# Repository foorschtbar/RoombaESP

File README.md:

# RoombaESP

This project is a Add-On PCB for the Roomba vacuum cleaner robots of series 500/600/700. It uses the open interface of the Roomba to control the robot via a ESP8266 microcontroller. The PCB is designed to be mounted on top in a 3D printed case and add

- MQTT
- REST API
- Monitoring Interface
- OLED Screen
- Status LED

## PCB

## Case & Features

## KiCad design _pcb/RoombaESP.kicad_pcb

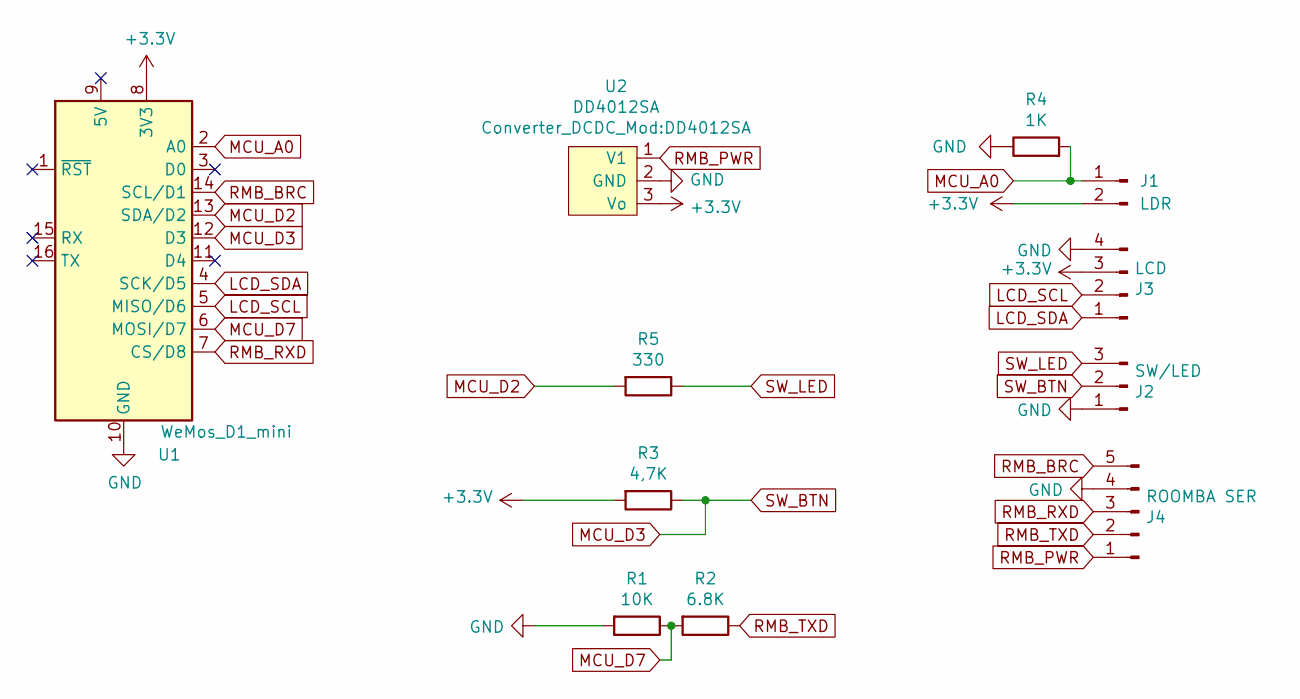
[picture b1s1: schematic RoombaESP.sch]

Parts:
J1: LDR; JST_PH_S2B-PH-K_1x02_P2.00mm_Horizontal
J2: SW/LED; JST_PH_S3B-PH-K_1x03_P2.00mm_Horizontal
J3: LCD; JST_PH_S4B-PH-K_1x04_P2.00mm_Horizontal
J4: ROOMBA SER; JST_PH_S5B-PH-K_1x05_P2.00mm_Horizontal
R1: 10K; R_0805_2012Metric_Pad1.20x1.40mm_HandSolder
R2: 6.8K; R_0805_2012Metric_Pad1.20x1.40mm_HandSolder
R3: 4,7K; R_0805_2012Metric_Pad1.20x1.40mm_HandSolder
R4: 1K; R_0805_2012Metric_Pad1.20x1.40mm_HandSolder
R5: 330; R_0805_2012Metric_Pad1.20x1.40mm_HandSolder
U1: WeMos_D1_mini; WEMOS_D1_mini_light
U2: DD4012SA

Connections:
+3V3: J1.2, J3.3, R3.2, U1.8 (3V3), U2.3 (Vo)
GND: J2.1, J3.4, J4.4, R1.2, R4.1, U1.10 (GND), U2.2 (GND)
LCD_SCL: J3.2, U1.5 (MISO/D6)
LCD_SDA: J3.1, U1.4 (SCK/D5)
MCU_A0: J1.1, R4.2, U1.2 (A0)
MCU_D2: R5.2, U1.13 (SDA/D2)
MCU_D3: J2.2, R3.1, U1.12 (D3)
MCU_D7: R1.1, R2.2, U1.6 (MOSI/D7)
RMB_BRC: J4.5, U1.14 (SCL/D1)
RMB_PWR: J4.1, U2.1 (V1)
RMB_RXD: J4.3, U1.7 (CS/D8)
RMB_TXD: J4.2, R2.1
SW_LED: J2.3, R5.1

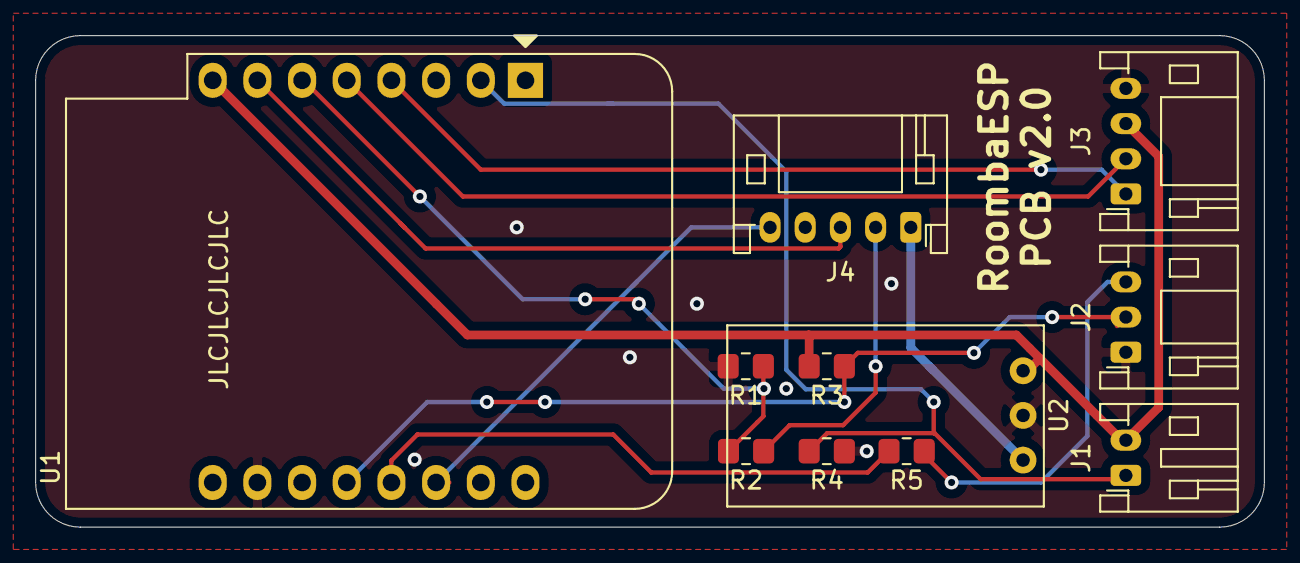
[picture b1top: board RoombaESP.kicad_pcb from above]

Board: 2 copper layers, 69.9 x 27.9 mm, 11 parts (0 on the bottom side), 13 nets.

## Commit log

2019-11-11 Fixes
2019-11-19 Fix sensor status problem with some yield()'s
2019-11-24 Finish API for Dock commands
2020-10-16 Rename Wifi signal quaility function and update .gitignore
2020-10-24 Implemented MQTT, removed REST API
2020-12-29 added oled boot screen
2020-12-29 removed travis ci file
2021-01-17 Added OLED Screen - add oled screen - remove log to SPIFF - other improvements
2021-01-17 Added Screen Switching and Timeout
2021-01-18 updates documentation
2021-01-19 Some improvments - added more screens - fix some issues with mqtt topics - add a lot of debug output to telnet - cleanup code
2021-01-22 Added KiCad PCB v1.0
2021-01-22 Added RoombaESP PCB v2.0
2021-01-22 Added README and PCB image
2021-05-22 Added Gerber files
2021-06-12 Updated PCB
2021-11-28 Added WiFi AutoReconnect
2021-11-28 Update Version
2023-05-26 Updated libs
2023-05-26 Added fancy led animation
2023-07-16 Make fancy led configurable
2023-07-16 Added brightness option
